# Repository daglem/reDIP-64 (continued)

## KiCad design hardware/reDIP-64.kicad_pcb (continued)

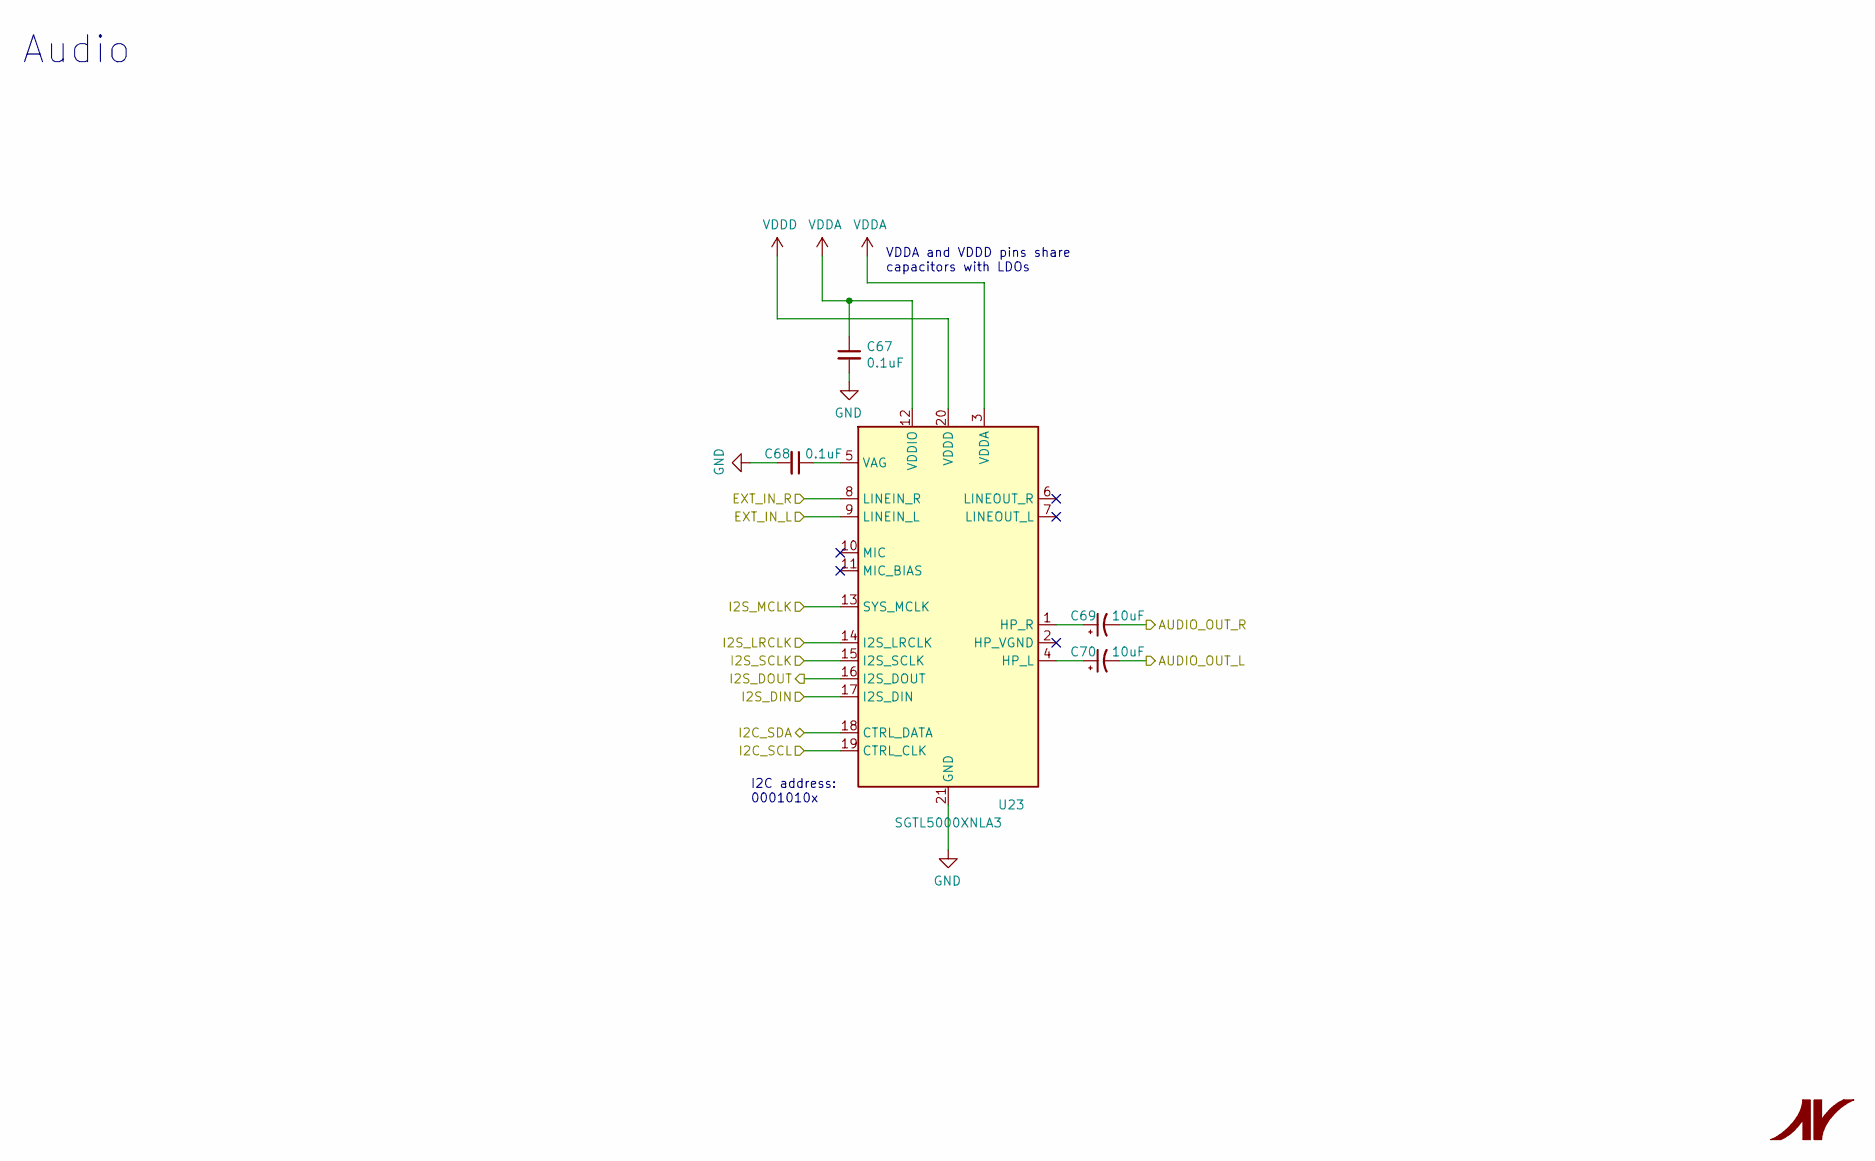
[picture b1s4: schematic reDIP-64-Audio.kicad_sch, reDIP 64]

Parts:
C67, C68: 0.1uF; C_0201_0603Metric
C69, C70: 10uF; CP_EIA-1608-08_AVX-J
U23: SGTL5000XNLA3; QFN-20-1EP_3x3mm_P0.4mm_EP1.65x1.65mm

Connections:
/Audio/AUDIO_OUT_L: C70.2; also elsewhere on the board
/Audio/AUDIO_OUT_R: C69.2; also elsewhere on the board
/Audio/EXT_IN_L: U23.9 (LINEIN_L); also elsewhere on the board
/Audio/EXT_IN_R: U23.8 (LINEIN_R); also elsewhere on the board
/Audio/I2C_SCL: U23.19 (CTRL_CLK); also elsewhere on the board
/Audio/I2C_SDA: U23.18 (CTRL_DATA); also elsewhere on the board
/Audio/I2S_DIN: U23.17 (I2S_DIN); also elsewhere on the board
/Audio/I2S_DOUT: U23.16 (I2S_DOUT); also elsewhere on the board
/Audio/I2S_LRCLK: U23.14 (I2S_LRCLK); also elsewhere on the board
/Audio/I2S_MCLK: U23.13 (SYS_MCLK); also elsewhere on the board
/Audio/I2S_SCLK: U23.15 (I2S_SCLK); also elsewhere on the board
GND: C67.2, C68.2, U23.21 (GND); also elsewhere on the board
unnamed: C70.1, U23.4 (HP_L)
unnamed: C69.1, U23.1 (HP_R)
unnamed: C68.1, U23.5 (VAG)
VDDA: C67.1, U23.3 (VDDA), U23.12 (VDDIO); also elsewhere on the board
VDDD: U23.20 (VDDD); also elsewhere on the board

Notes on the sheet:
VDDA and VDDD pins share capacitors with LDOs
I2C address: 0001010x
Audio

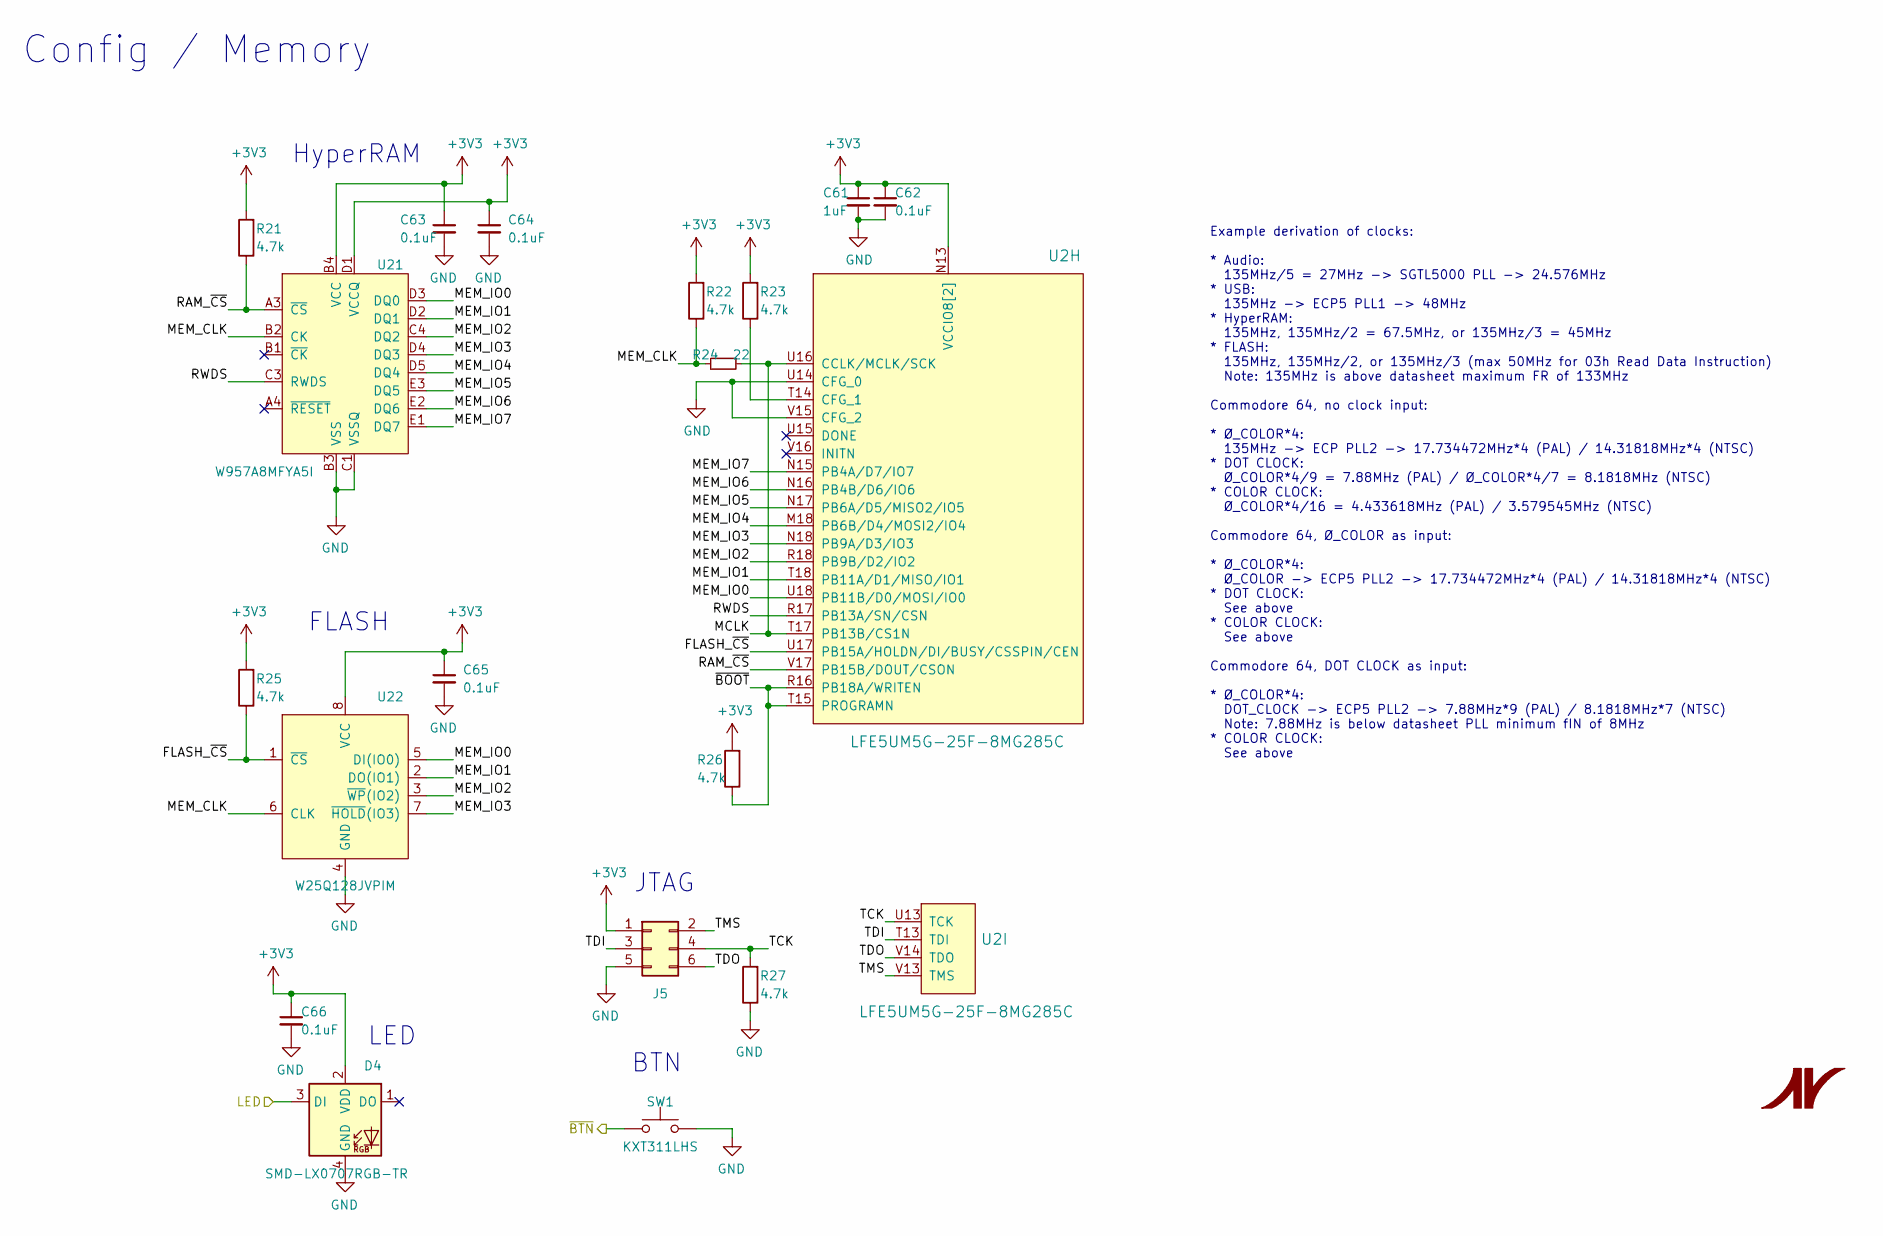
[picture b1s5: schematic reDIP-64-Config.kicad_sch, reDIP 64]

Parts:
C61: 1uF; C_0201_0603Metric
C62, C63, C64, C65, C66: 0.1uF; C_0201_0603Metric
D4: SMD-LX0707RGB-TR
J5: Conn_02x05_Odd_Even; PinHeader_2x03_P1.27mm_Vertical
R21, R22, R23, R25, R26, R27: 4.7k; R_0201_0603Metric
R24: 22; R_0201_0603Metric
SW1: KXT311LHS; SW_SPST_CK_KXT3
U2: LFE5UM5G-25F-8MG285C; BGA-285_10x10mm_P0.5mm
U21: W957A8MFYA5I; TFBGA-24_6.0x8.0mm_P1mm
U22: W25Q128JVPIM; WSON-8-1EP_6x5mm_P1.27mm_EP3.4x4.3mm

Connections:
+3V3: C61.1, C62.1, C63.1, C64.1, C65.1, C66.1, D4.2 (VDD), J5.1, R21.2, R22.2, R23.2, R25.2, R26.2, U2.N13 (VCCIO8[2]), U2.P14 (VCCIO8[2]), U21.B4 (VCC), U21.D1 (VCCQ), U21.E4 (VCCQ), U22.8 (VCC); also elsewhere on the board
/Config_Memory/FLASH_~CS: R25.1, U2.U17 (PB15A/HOLDN/DI/BUSY/CSSPIN/CEN), U22.1 (~CS)
/Config_Memory/LED: D4.3 (DI); also elsewhere on the board
/Config_Memory/MCLK: R24.1, U2.T17 (PB13B/CS1N), U2.U16 (CCLK/MCLK/SCK)
/Config_Memory/MEM_CLK: R22.1, R24.2, U21.B2 (CK), U22.6 (CLK)
/Config_Memory/MEM_IO0: U2.U18 (PB11B/D0/MOSI/IO0), U21.D3 (DQ0), U22.5 (DI(IO0))
/Config_Memory/MEM_IO1: U2.T18 (PB11A/D1/MISO/IO1), U21.D2 (DQ1), U22.2 (DO(IO1))
/Config_Memory/MEM_IO2: U2.R18 (PB9B/D2/IO2), U21.C4 (DQ2), U22.3 (~WP(IO2))
/Config_Memory/MEM_IO3: U2.N18 (PB9A/D3/IO3), U21.D4 (DQ3), U22.7 (~HOLD(IO3))
/Config_Memory/MEM_IO4: U2.M18 (PB6B/D4/MOSI2/IO4), U21.D5 (DQ4)
/Config_Memory/MEM_IO5: U2.N17 (PB6A/D5/MISO2/IO5), U21.E3 (DQ5)
/Config_Memory/MEM_IO6: U2.N16 (PB4B/D6/IO6), U21.E2 (DQ6)
/Config_Memory/MEM_IO7: U2.N15 (PB4A/D7/IO7), U21.E1 (DQ7)
/Config_Memory/RAM_~CS: R21.1, U2.V17 (PB15B/DOUT/CSON), U21.A3 (~CS)
/Config_Memory/RWDS: U2.R17 (PB13A/SN/CSN), U21.C3 (RWDS)
/Config_Memory/TCK: J5.4, R27.2, U2.U13 (TCK)
/Config_Memory/TDI: J5.3, U2.T13 (TDI)
/Config_Memory/TDO: J5.6, U2.V14 (TDO)
/Config_Memory/TMS: J5.2, U2.V13 (TMS)
/Config_Memory/~BOOT: R26.1, U2.R16 (PB18A/WRITEN), U2.T15 (PROGRAMN)
/FPGA_IO/~BTN: SW1.1; also elsewhere on the board
GND: C61.2, C62.2, C63.2, C64.2, C65.2, C66.2, D4.4 (GND), J5.5, R27.1, SW1.2, U2.U14 (CFG_0), U2.V15 (CFG_2), U21.B3 (VSS), U21.C1 (VSSQ), U21.E5 (VSSQ), U22.4 (GND), U22.9 (GND); also elsewhere on the board
unnamed: R23.1, U2.T14 (CFG_1)

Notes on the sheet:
HyperRAM
FLASH
Config / Memory
Example derivation of clocks: * Audio: 135MHz/5 = 27MHz -> SGTL5000 PLL -> 24.576MHz * USB: 135MHz -> ECP5 PLL1 -> 48MHz * HyperRAM: 135MHz, 135MHz/2 = 67.5MHz, or 135MHz/3 = 45MHz * FLASH: 135MHz, 135MHz/2, or 135MHz/3 (max 50MHz for 03h Read Data Instruction) Note: 135MHz is above datasheet maxim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
JTAG
BTN
LED

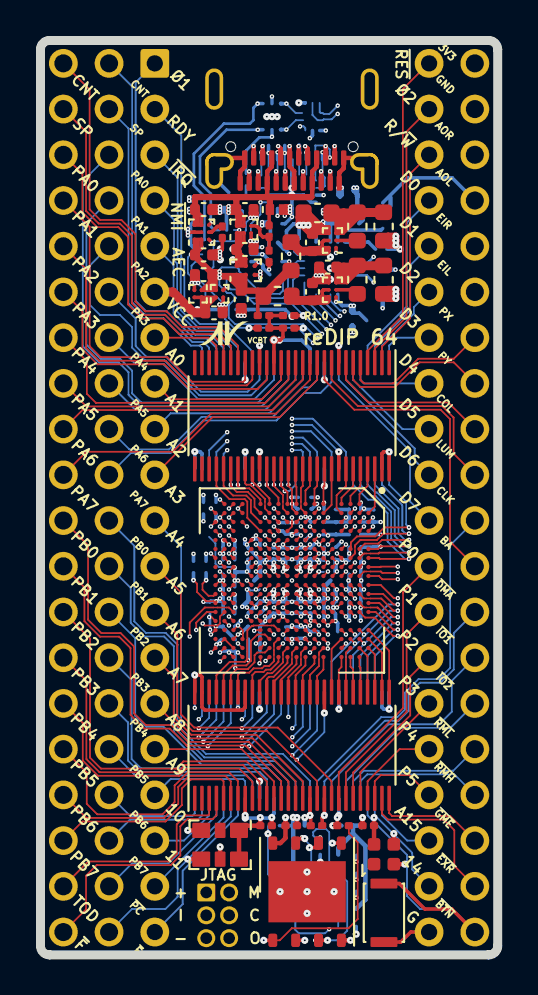
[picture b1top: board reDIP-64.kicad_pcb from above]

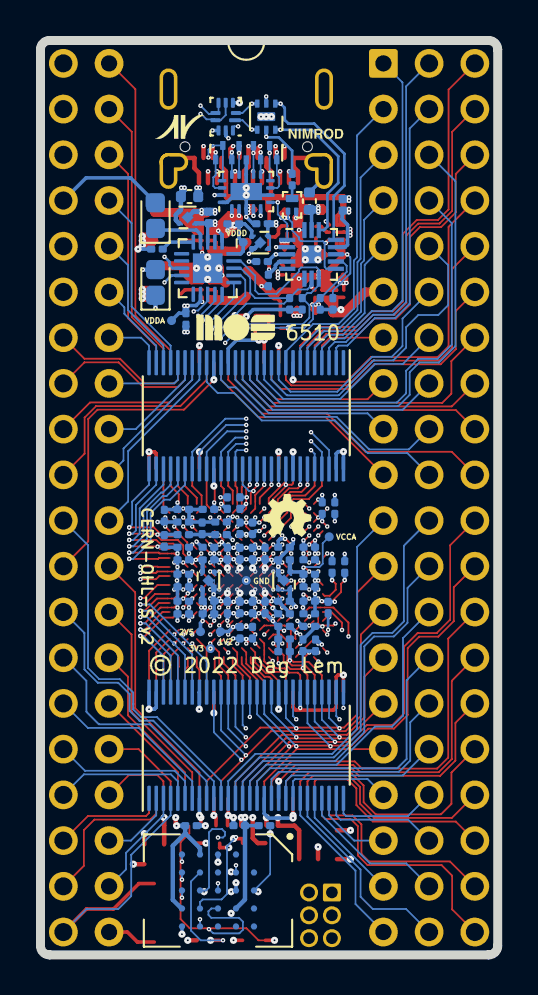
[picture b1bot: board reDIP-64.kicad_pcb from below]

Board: 6 copper layers, 25.4 x 50.8 mm, 150 parts (100 on the bottom side), 279 nets.

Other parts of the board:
OSHW logo: G***; OSHW-logo
svg2mod, svg2mod#3: G***; Nimrod-N-small
svg2mod#2: G***; Nimrod-text-small
svg2mod#4: G***; MOS-logo-small

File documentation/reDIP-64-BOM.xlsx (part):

Prj: | reDIP 64 |  |  |  |  |  |  | Board Qty: | 100
Co.: | Nimrod |  |  |  |  |  |  | Unit Cost: | 30.4541
Prj date: | lø. 23. april 2022 kl. 17.23 +0200 |  |  |  |  |  |  | Total Cost: | 3045.4149 |  |  |  |  | 1220.08 | 22 of 53 parts found |  |  |  |  | 3181.628 | 52 of 53 parts found |  |  |  |  | 1467.2582 | 38 of 53 parts found |  |  |  |  | 209.65 | 11 of 53 parts found |  |  |  |  | 2558.3 | 45 of 53 parts found |  |  |  |  | 1634.9 | 39 of 53 parts found |  |  |  |  | 346.1956 | 18 of 53 parts found |  |  |  |  | 60.6371 | 4 of 53 parts found
$ date: | 2022-04-23 17:23:41
Global Part Info |  |  |  |  |  |  |  |  |  | Arrow |  |  |  |  |  | Digi-Key |  |  |  |  |  | Farnell |  |  |  |  |  | LCSC |  |  |  |  |  | Mouser |  |  |  |  |  | Newark |  |  |  |  |  | RS Components |  |  |  |  |  | TME
Refs | Value | Desc | Notes | Footprint | Manf | Manf# | Qty | Unit$ | Ext$ | Avail | Purch | Unit$ | MOQ | Ext$ | Cat# | Avail | Purch | Unit$ | MOQ | Ext$ | Cat# | Avail | Purch | Unit$ | MOQ | Ext$ | Cat# | Avail | Purch | Unit$ | MOQ | Ext$ | Cat# | Avail | Purch | Unit$ | MOQ | Ext$ | Cat# | Avail | Purch | Unit$ | MOQ | Ext$ | Cat# | Avail | Purch | Unit$ | MOQ | Ext$ | Cat# | Avail | Purch | Unit$ | MOQ | Ext$ | Cat#
C1,C13,C19 | 1uF | CAP CER 2.2uF 25V 20% X5R 0402 | 5V DC DERATED TO 1uF | C_0402_1005Metric | Murata | GRM155R61E225ME11D | 300 | 0.0352 | 10.56 | 41127 |  | 0.0921 | 1 | 27.63 | GRM155R61E225ME11D | 163798 |  | 0.0961 | 1 | 28.83 | 490-12704-1-ND | 20000 |  | 0.09924444444444445 | 10 | 29.7733 | 3582801 | 6980 |  | 0.0352 | 10 | 10.56 | C385033 | 247394 |  | 0.1 | 1 | 30.0 | 81GRM155R61E225ME1D | 20000 |  | 0.1 | 1 | 30.0 | 03AJ1583
C2,C4,C24,C26,C30,C31,C37,C39,C41,C43,C45,C47,C49,C51,C53,C55,C57,C61 | 1uF | CAP CER 2.2uF 6.3V 20% X5R 0201 | C24,C30: 1.2V DC DERATED TO 1.4uF C26: 2.5V DC DERATED TO 0.9uF C2,C4,C31,C37,C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 | C_0201_0603Metric | Murata | GRM033R60J225ME01D | 1800 | 0.0288 | 51.84 |  |  |  |  |  |  | 11380 |  | 0.03795 | 1 | 68.31 | 490-GRM033R60J225ME01DCT-ND |  |  |  |  |  |  | 12020 |  | 0.0288 | 10 | 51.84 | C782150 | 670 |  | 0.044 | 1 | 79.2 | 81GRM033R60J225ME1D
C3,C23,C25,C28,C29 | 1uF | CAP CER 2.2uF 10V 20% X5R 0201 | C23,C25,C28,C29: 3.3V DC DERATED TO 0.9uF C3: 5V DC DERATED TO 0.6uF | C_0201_0603Metric | Murata | GRM035R61A225ME01D | 500
C5,C7-C11 | 100nF | CAP CER 100nF 6.3V 10% X5R 0201 |  | C_0201_0603Metric | Murata | GRM033R60J104KE19D | 600 | 0.002 | 1.2 | 3960000 |  |  | 15000 |  | GRM033R60J104KE19D | 30960551 |  | 0.00642 | 1 | 3.852 | 490-3167-1-ND | 105000 |  | 0.049493333333333334 | 10 | 29.696 | 1775994 | 2617600 |  | 0.002 | 100 | 1.2 | C76928 | 6447225 |  | 0.009 | 1 | 5.4 | 81GRM033R60J104KE19 | 105000 |  | 0.012 | 1 | 7.2 | 51R6558 |  |  |  |  |  |  | 25600 |  | 0.012502222222222224 | 100 | 7.5013 | GRM033R60J104KE19D
C6,C32-C36,C38,C40,C42,C44,C46,C48,C50,C52,C54,C56,C58-C60,C62-C68 | 0.1uF | CAP CER 0.22uF 6.3V 20% X5R 0201 | C68: 1.5V DC VAG DERATED TO 0.1uF C6,C32-C36,C38,C40,C42,C44,C46,C48,C50,C52,C5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 | C_0201_0603Metric | Murata | GRM033R60J224KE15D | 2600 | 0.0036 | 9.36 | 115702 |  |  | 15000 |  | GRM033R60J224KE15D | 2560342 |  | 0.00742 | 1 | 19.292 | 490-10406-1-ND | 210000 |  | 0.006702222222222222 | 10 | 17.4258 | 2990684 | 21400 |  | 0.0036 | 100 | 9.36 | C76931 | 350207 |  | 0.009 | 1 | 23.4 | 81GRM33R60J224KE15D | 210000 |  | 0.015 | 1 | 39.0 | 94AC8892 | 21000 |  | 0.009022222222222223 | 1000 | 23.4578 | 1852023
C12,C21 | 2.2uF | CAP CER 10uF 6.3V 20% X5R 0402 | 5V DC DERATED TO 1.9uF | C_0402_1005Metric | Murata | GRM155R60J106ME05J | 200 | 0.0367 | 7.34 |  |  |  |  |  |  | NonStk |  | 0.0367 | 1 | 7.34 | 490-GRM155R60J106ME05JCT-ND | NonStk |  |  | 40000 |  | 3785797 |  |  |  |  |  |  | 19303 |  | 0.039 | 1 | 7.8 | 81GRM155R60J106ME05
C14-C17,C20,C27 | 1uF | CAP CER 2.2uF 16V 10% X6S 0402 | 5V DC DERATED TO 1uF | C_0402_1005Metric | Murata | GRM155C81C225KE11D | 600 | 0.05928888888888889 | 35.5733 | 9005 |  | 0.0924 | 1 | 55.44 | GRM155C81C225KE11D | 21504 |  | 0.06578 | 1 | 39.468 | 490-14595-1-ND | 45449 |  | 0.05928888888888889 | 10 | 35.5733 | 3581345 |  |  |  |  |  |  | 2615 |  | 0.097 | 1 | 58.2 | 81GRM155C81C225KE1D | 45429 |  | 0.097 | 10 | 58.2 | 92AH5000
C18 | 10uF | CAP CER 22uF 6.3V 20% X5R 0603 | 3.3V DC DERATED TO 8uF | C_0603_1608Metric | Murata | GRM188R60J226ME15D | 100 | 0.0511 | 5.11 | 15798 |  | 0.1207 | 1 | 12.07 | GRM188R60J226ME15D | 9752 |  | 0.0748 | 1 | 7.48 | 490-GRM188R60J226ME15DCT-ND | 11110 |  | 0.116 | 10 | 11.6 | 3581375 | 6610 |  | 0.0511 | 10 | 5.11 | C440187 | 2004 |  | 0.118 | 1 | 11.8 | 81GRM188R60J226ME5D | 11110 |  | 0.118 | 10 | 11.8 | 92AH5101
C22 | 10uF | CAP CER 10uF 4V 20% X5R 0402 | 1.2V DC DERATED TO 7.5uF | C_0402_1005Metric | Murata | GRM155R60G106ME01D | 100 | 0.046 | 4.6 |  |  |  |  |  |  | NonStk |  |  | 10000 |  | 490-GRM155R60G106ME01DTR-ND | NonStk |  |  | 10000 |  | 3785795 |  |  |  |  |  |  | NonStk |  | 0.046 | 1 | 4.6 | 81GRM155R60G106ME1D
C69,C70 | 10uF | CAP TANT 10uF 6.3V 20% 0603 | 1.65V DC 1.5V AC AUDIO | CP_EIA-1608-08_AVX-J | Vishay | TMCJ0J106MTRF | 200 | 0.15337777777777778 | 30.6756 |  |  |  |  |  |  | NonStk |  | 0.1618 | 1 | 32.36 | 718-2355-1-ND | NonStk |  | 0.16626666666666667 | 10 | 33.2533 | 2491414 |  |  |  |  |  |  | NonStk |  | 0.162 | 1 | 32.4 | 74TMCJ0J106MTRF | NonStk |  | 0.162 | 10 | 32.4 | 56Y0084 | 20 |  | 0.15337777777777778 | 20 | 30.6756 | 1882240
D1 | ESD7241 | DIODE ESD VRWM 24V X2DFN2 |  | CASE_714AB_1.0x0.6mm | onsemi | ESD7241N2T5G | 100 | 0.172 | 17.2 |  |  |  |  |  |  | NonStk |  | 0.2056 | 1 | 20.56 | ESD7241N2T5GOSCT-ND | NonStk |  | 0.27066666666666667 | 5 | 27.0667 | 3368198 |  |  |  |  |  |  | 3983 |  | 0.206 | 1 | 20.6 | 863ESD7241N2T5G | NonStk |  | 0.172 | 1 | 17.2 | 54AH8588
D2 | VESD05A6-HAF | IC ESD ARRAY VRWM 5V LLP75-7L |  | LLP75-7L | Vishay | VESD05A6-HAF-GS08 | 100 | 0.1527 | 15.27 | 14503 |  | 0.3194 | 1 | 31.94 | VESD05A6HAFGS08 | 2 |  | 0.3542 | 1 | 35.42 | VESD05A6-HAF-GS08GICT-ND |  |  |  |  |  |  | 15000 |  | 0.1527 | 1 | 15.27 | C1974940 | 2755 |  | 0.355 | 1 | 35.5 | 78VESD05A6HAF | NonStk |  |  | 15000 |  | 64M7155 | 120 |  | 0.35960000000000003 | 20 | 35.96 | 1808156
D3 | D3V3F8U9LP3810 | IC ESD ARRAY VRWM 3.3V U-DFN3810-09 |  | U-DFN3810-9 | Diodes | D3V3F8U9LP3810-7 | 100 | 0.166 | 16.6 | 757 |  | 0.1816 | 1 | 18.16 | D3V3F8U9LP38107 | 515 |  | 0.2194 | 1 | 21.94 | D3V3F8U9LP3810-7DICT-ND |  |  |  |  |  |  |  |  |  |  |  |  | 1234 |  | 0.22 | 1 | 22.0 | 621D3V3F8U9LP38107 | NonStk |  | 0.166 | 5 | 16.6 | 28AK9075 | 752 |  | 0.32093333333333335 | 50 | 32.0933 | 1827487
D4 | SMD-LX0707RGB-TR | IC LED RGB 0707 | REPLACEMENT PARTS: Everlight 19-C47/RSGHBHC-5V01/2T, Everlight EAST1818RGBICA0 | SMD-LX0707RGB-TR | Lumex | SMD-LX0707RGB-TR | 100 | 0.23612444444444447 | 23.6124 |  |  |  |  |  |  | 95408 |  | 0.3145 | 1 | 31.45 | 67-2331-1-ND | NonStk |  | 0.44724444444444444 | 1 | 44.7244 | 3216559 |  |  |  |  |  |  | 1129 |  | 0.315 | 1 | 31.5 | 696SMDLX0707RGBTR | NonStk |  | 0.315 | 1 | 31.5 | 02AH5948 |  |  |  |  |  |  | NonStk |  | 0.23612444444444447 | 1 | 23.6124 | SMDLX0707RGBTR
FB1-FB4 | BLM18KG601SN1 | FERRITE BEAD 600Ω 1.3A 0603 |  | L_0603_1608Metric | Murata | BLM18KG601SN1D | 400 | 0.0171 | 6.84 |  |  |  |  |  |  | NonStk |  | 0.038 | 1 | 15.2 | 490-5258-1-ND | NonStk |  | 0.03222222222222223 | 10 | 12.8889 | 1781094 | 237800 |  | 0.0171 | 50 | 6.84 | C85833 | NonStk |  | 0.035 | 1 | 14.0 | 81BLM18KG601SN1D | NonStk |  | 0.035 | 1 | 14.0 | 55R1514 | NonStk |  | 0.03222222222222223 | 100 | 12.8889 | 7474720 | 2850 |  | 0.04980266666666667 | 50 | 19.9211 | BLM18KG601SN1D
J1 | USB4080 | CONN USB-C | REPLACEMENT PART: HRO TYPE-C-31-M-05 | USB_C_Receptacle_GCT_USB4080 | GCT | USB4080-03-A | 100 | 0.616 | 61.6 |  |  |  |  |  |  | NonStk |  | 0.924 | 1 | 92.4 | 2073-USB4080-03-ACT-ND | NonStk |  | 0.7565777777777778 | 1 | 75.6578 | 3801072 |  |  |  |  |  |  | 1590 |  | 0.879 | 1 | 87.9 | 640USB408003A | 1575 |  | 0.616 | 1 | 61.6 | 59AJ3622
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
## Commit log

2021-05-09 File cleanup
2021-06-12 Various improvements
    * Removed slash from sheet names
    * Reannotated schematics
    * Example derivation of clocks in schematics
    * Identical capacitors for DisplayPort main lanes and AUX
    * Replaced switch FSA2259UMX with FSUSB42UMX
    * Modified PCB physical stackup to (hopefully) be manufacturable
2021-06-12 Corrected BOM for C1-C6
2021-06-16 Added stitching vias and test points
    Thanks to @azonenberg for help and suggestions.
2022-03-10 Updated all KiCad files to current format
2022-04-10 Revision 1.0
    * USB receptacle replaced with GCT USB4080-03-A / HRO TYPE-C-31-M-05
    * USB PD TCPC changed to PTN5110NHQ (FPF2286 has 15ms VBUS debounce time)
    * Complete rework of power section
    - Over-voltage protection on VBUS (FPF2286 / FPF2495C)
    - Bidirectional VCC (2 x TPS22916)
    - Replaced EOLed buck converters with FAN53610 / FAN53611
2022-04-13 Replaced socket pin headers with socket adapter
    The socket adapter should hopefully *just* fit.
2022-04-14 A few improvements
    * Changed MCLK pullup to 4.7k
    * A few pin swaps for cleaner routing
    * Example pin headers in BOM
    * Replaced reduced lifetime "mobile only" capacitors
2022-04-15 BOM correction, silk screen update
2022-04-23 Audio upgrade
    * Changed from line out to headphone out with 10uF tantalum capacitors
    * PTN5110 decoupling capacitor QA
2022-04-24 Further audio improvements
    * Additional power supply vias
    * Moved power and headphone out tracks away from under buck converters
2022-12-26 Global symbol update
2024-03-09 Updated to KiCad 7
